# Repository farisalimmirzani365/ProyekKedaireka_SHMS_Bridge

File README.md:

# PCB-Desain Structur Health Monitoring System
Proyek Kedaireka "Solusi IoT untuk Memantau Kondisi Infrastruktur Jembatan". Kedaireka adalah proyek penelitian matching fund oleh Kementerian Pendidikan, Kebudayaan, Riset, dan Teknologi antara PT. INTI & Telkom University.

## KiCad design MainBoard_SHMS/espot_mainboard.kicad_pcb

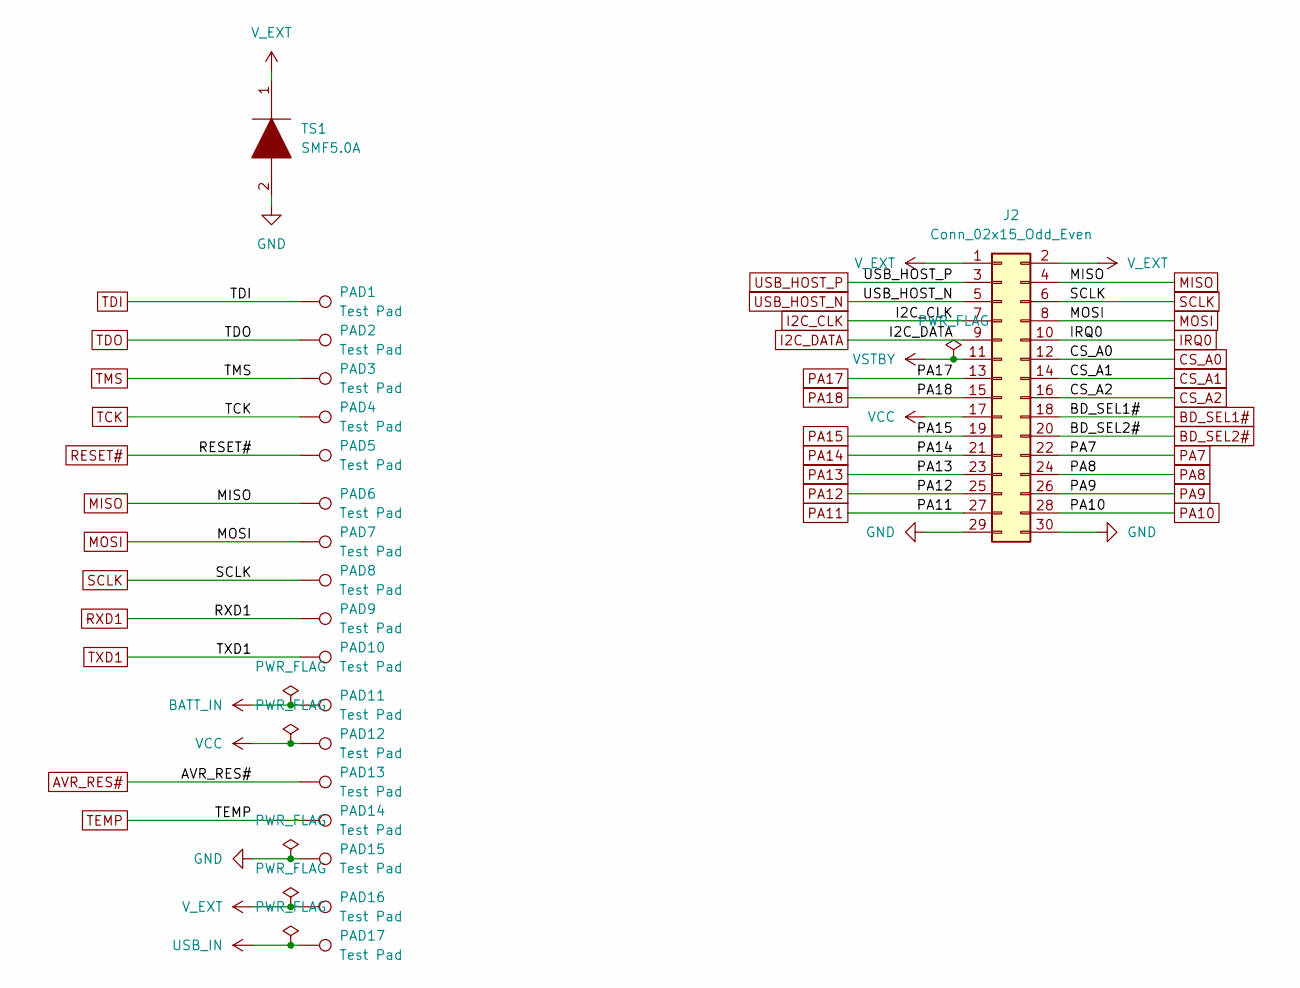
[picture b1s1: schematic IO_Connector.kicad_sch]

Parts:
J2: Conn_02x15_Odd_Even; PinHeader_2x15_P2.54mm_Vertical
PAD1, PAD2, PAD3, PAD4, PAD5, PAD6, PAD7, PAD8, PAD9, PAD10, PAD11, PAD12, PAD13, PAD14, PAD15, PAD16, PAD17: Test Pad; TestPoint_Pad_D4.0mm
TS1: SMF5.0A; SODFL3618X110N; Manufacturer_Part_Number SMF5.0A; Mouser Part Number 576-SMF5.0A

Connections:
AVR_RES#: PAD13.1; also elsewhere on the board
BATT_IN: PAD11.1; also elsewhere on the board
BD_SEL1#: J2.18; also elsewhere on the board
BD_SEL2#: J2.20; also elsewhere on the board
CS_A0: J2.12; also elsewhere on the board
CS_A1: J2.14; also elsewhere on the board
CS_A2: J2.16; also elsewhere on the board
GND: J2.29, J2.30, PAD15.1, TS1.2; also elsewhere on the board
I2C_CLK: J2.7; also elsewhere on the board
I2C_DATA: J2.9; also elsewhere on the board
IRQ0: J2.10; also elsewhere on the board
MISO: J2.4, PAD6.1; also elsewhere on the board
MOSI: J2.8, PAD7.1; also elsewhere on the board
PA7: J2.22; also elsewhere on the board
PA8: J2.24; also elsewhere on the board
PA9: J2.26; also elsewhere on the board
PA10: J2.28; also elsewhere on the board
PA11: J2.27; also elsewhere on the board
PA12: J2.25; also elsewhere on the board
PA13: J2.23; also elsewhere on the board
PA14: J2.21; also elsewhere on the board
PA15: J2.19; also elsewhere on the board
PA17: J2.13; also elsewhere on the board
PA18: J2.15; also elsewhere on the board
RESET#: PAD5.1; also elsewhere on the board
RXD1: PAD9.1; also elsewhere on the board
SCLK: J2.6, PAD8.1; also elsewhere on the board
TCK: PAD4.1; also elsewhere on the board
TDI: PAD1.1; also elsewhere on the board
TDO: PAD2.1; also elsewhere on the board
TEMP: PAD14.1; also elsewhere on the board
TMS: PAD3.1; also elsewhere on the board
TXD1: PAD10.1; also elsewhere on the board
USB_HOST_N: J2.5; also elsewhere on the board
USB_HOST_P: J2.3; also elsewhere on the board
USB_IN: PAD17.1; also elsewhere on the board
VCC: J2.17, PAD12.1; also elsewhere on the board
VSTBY: J2.11; also elsewhere on the board
V_EXT: J2.1, J2.2, PAD16.1, TS1.1; also elsewhere on the board

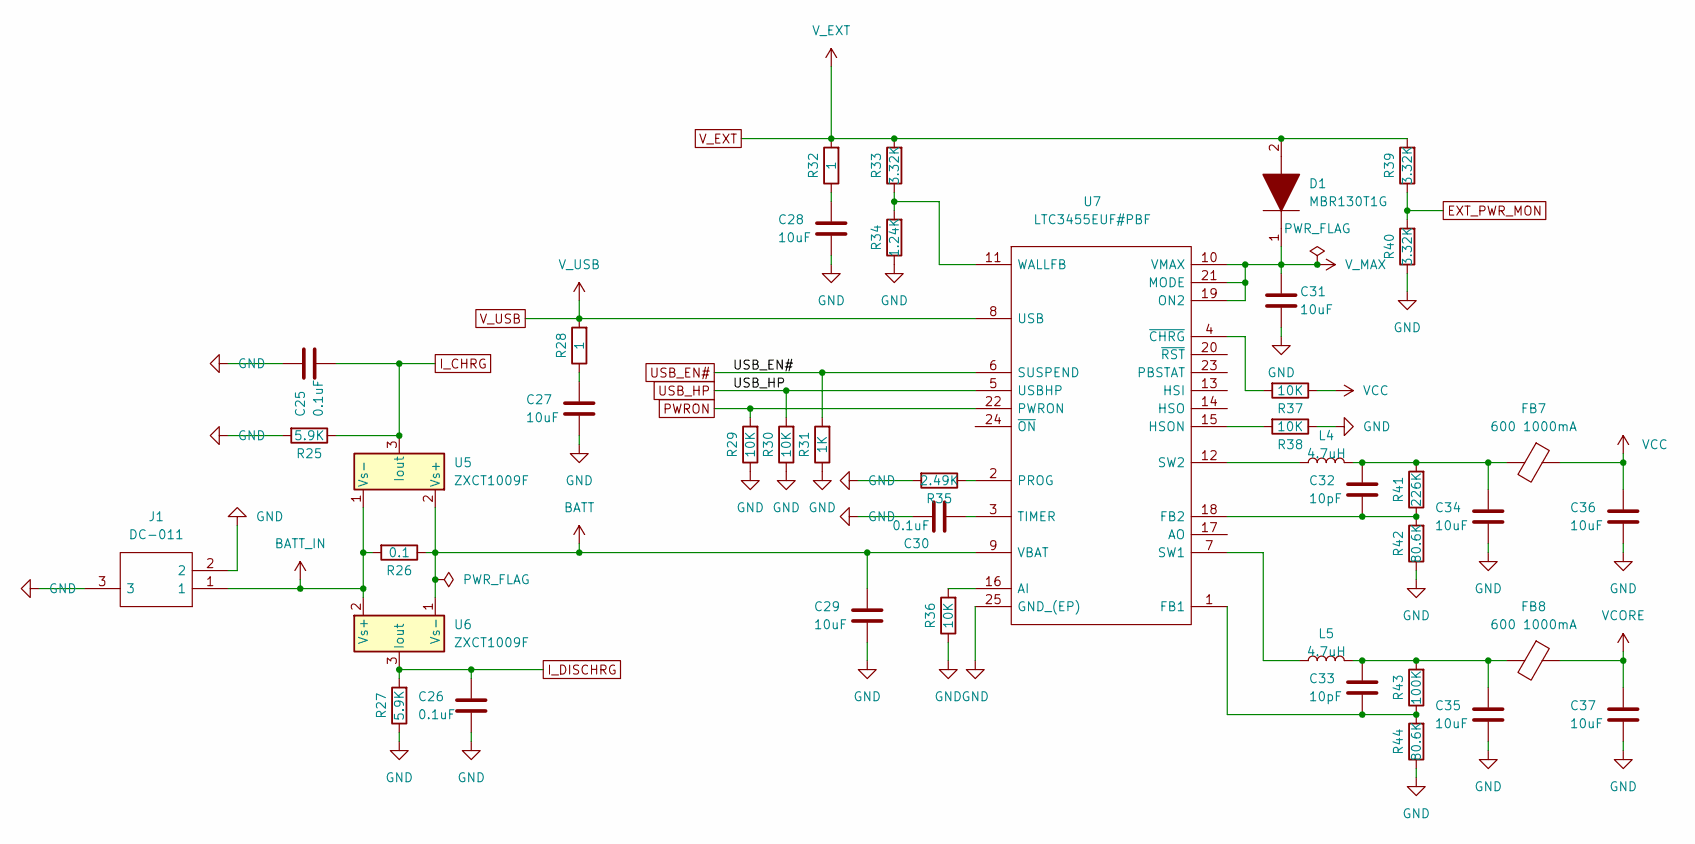
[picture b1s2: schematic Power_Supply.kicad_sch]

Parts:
C25, C26, C30: 0.1uF; C_0603_1608Metric_Pad1.08x0.95mm_HandSolder
C27, C28, C29, C31, C34, C35, C36, C37: 10uF; C_0603_1608Metric_Pad1.08x0.95mm_HandSolder
C32, C33: 10pF; C_0603_1608Metric_Pad1.08x0.95mm_HandSolder
D1: MBR130T1G; SOD3716X135N; Manufacturer_Part_Number MBR130T1G; Mouser Part Number 863-MBR130T1G
FB7, FB8: 600 1000mA; L_0603_1608Metric_Pad1.05x0.95mm_HandSolder
J1: DC-011; DC011; Manufacturer_Part_Number DC-011
L4, L5: 4.7uH; L_12x12mm_H6mm
R25, R27: 5.9K; R_0603_1608Metric_Pad0.98x0.95mm_HandSolder
R26: 0.1; R_0603_1608Metric_Pad0.98x0.95mm_HandSolder
R28, R32: 1; R_0603_1608Metric_Pad0.98x0.95mm_HandSolder
R29, R30, R36, R37, R38: 10K; R_0603_1608Metric_Pad0.98x0.95mm_HandSolder
R31: 1K; R_0603_1608Metric_Pad0.98x0.95mm_HandSolder
R33, R39, R40: 3.32K; R_0603_1608Metric_Pad0.98x0.95mm_HandSolder
R34: 1.24K; R_0603_1608Metric_Pad0.98x0.95mm_HandSolder
R35: 2.49K; R_0603_1608Metric_Pad0.98x0.95mm_HandSolder
R41: 226K; R_0603_1608Metric_Pad0.98x0.95mm_HandSolder
R42, R44: 80.6K; R_0603_1608Metric_Pad0.98x0.95mm_HandSolder
R43: 100K; R_0603_1608Metric_Pad0.98x0.95mm_HandSolder
U5, U6: ZXCT1009F; SOT-23
U7: LTC3455EUF#PBF; QFN50P400X400X80-25N-D; Manufacturer_Part_Number LTC3455EUF#PBF; Mouser Part Number 584-LTC3455EUF#PBF

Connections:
BATT: C29.1, R26.1, U5.2 (Vs+), U6.1 (Vs-), U7.9 (VBAT); also elsewhere on the board
BATT_IN: J1.1, R26.2, U5.1 (Vs-), U6.2 (Vs+); also elsewhere on the board
EXT_PWR_MON: R39.1, R40.2; also elsewhere on the board
GND: C25.1, C26.2, C27.2, C28.2, C29.2, C30.1, C31.2, C34.2, C35.2, C36.2, C37.2, J1.2, J1.3, R25.2, R27.1, R29.1, R30.1, R31.1, R34.1, R35.2, R36.1, R38.1, R40.1, R42.1, R44.1, U7.25 (GND_(EP)); also elsewhere on the board
I_CHRG: C25.2, R25.1, U5.3 (Iout); also elsewhere on the board
I_DISCHRG: C26.1, R27.2, U6.3 (Iout); also elsewhere on the board
unnamed: C27.1, R28.1
unnamed: C28.1, R32.1
unnamed: C30.2, U7.3 (TIMER)
unnamed: C32.1, C34.1, FB7.2, L4.2, R41.2
unnamed: C32.2, R41.1, R42.2, U7.18 (FB2)
unnamed: C33.1, C35.1, FB8.2, L5.2, R43.2
unnamed: C33.2, R43.1, R44.2, U7.1 (FB1)
unnamed: L4.1, U7.12 (SW2)
unnamed: L5.1, U7.7 (SW1)
unnamed: R33.1, R34.2, U7.11 (WALLFB)
unnamed: R35.1, U7.2 (PROG)
unnamed: R36.2, U7.16 (AI)
unnamed: R37.2, U7.4 (~CHRG)
unnamed: R38.2, U7.15 (HSON)
PWRON: R29.2, U7.22 (PWRON); also elsewhere on the board
USB_EN#: R31.2, U7.6 (SUSPEND); also elsewhere on the board
USB_HP: R30.2, U7.5 (USBHP); also elsewhere on the board
USB_IN: R28.2, U7.8 (USB); also elsewhere on the board
VCC: C36.1, FB7.1, R37.1; also elsewhere on the board
VCORE: C37.1, FB8.1; also elsewhere on the board
V_EXT: D1.2, R32.2, R33.2, R39.2; also elsewhere on the board
V_MAX: C31.1, D1.1, U7.10 (VMAX), U7.19 (ON2), U7.21 (MODE); also elsewhere on the board

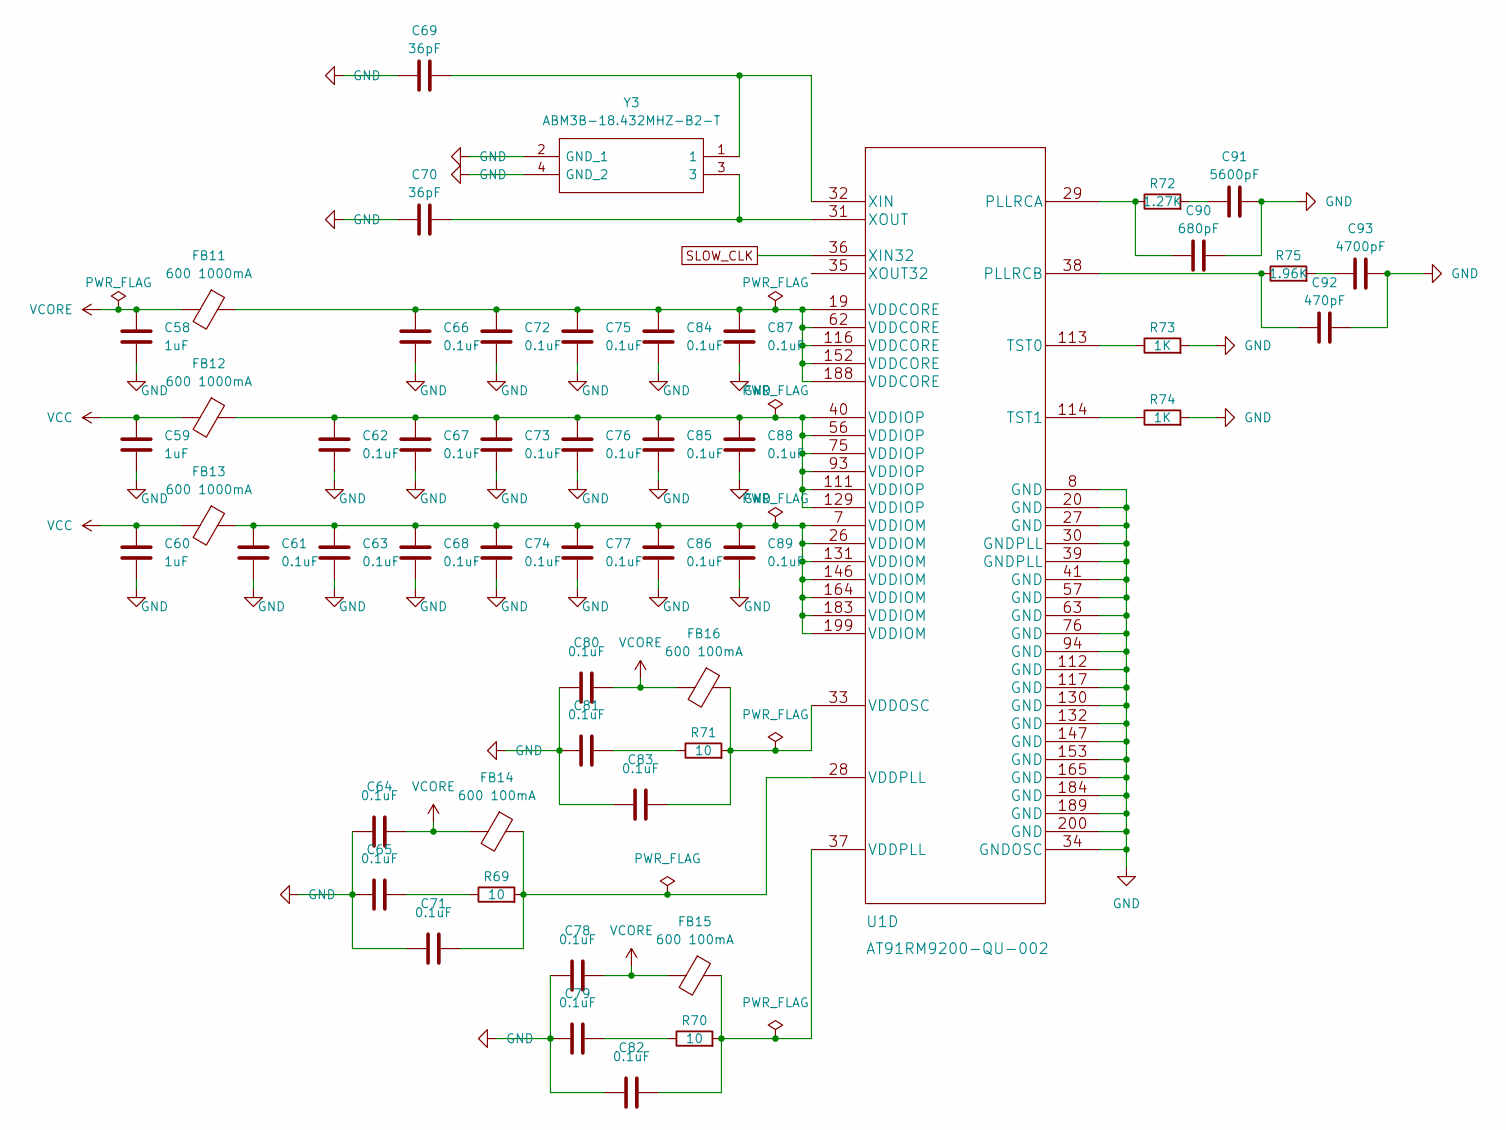
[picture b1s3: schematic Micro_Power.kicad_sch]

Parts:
C58, C59, C60: 1uF; C_0603_1608Metric_Pad1.08x0.95mm_HandSolder
C61, C62, C63, C64, C65, C66, C67, C68, C71, C72, C73, C74, C75, C76, C77, C78, C79, C80, C81, C82, C83, C84, C85, C86, C87, C88, C89: 0.1uF; C_0603_1608Metric_Pad1.08x0.95mm_HandSolder
C69, C70: 36pF; C_0603_1608Metric_Pad1.08x0.95mm_HandSolder
C90: 680pF; C_0603_1608Metric_Pad1.08x0.95mm_HandSolder
C91: 5600pF; C_0603_1608Metric_Pad1.08x0.95mm_HandSolder
C92: 470pF; C_0603_1608Metric_Pad1.08x0.95mm_HandSolder
C93: 4700pF; C_0603_1608Metric_Pad1.08x0.95mm_HandSolder
FB11, FB12, FB13: 600 1000mA; L_0603_1608Metric_Pad1.05x0.95mm_HandSolder
FB14, FB15, FB16: 600 100mA; L_0402_1005Metric_Pad0.77x0.64mm_HandSolder
R69, R70, R71: 10; R_0603_1608Metric_Pad0.98x0.95mm_HandSolder
R72: 1.27K; R_0603_1608Metric_Pad0.98x0.95mm_HandSolder
R73, R74: 1K; R_0603_1608Metric_Pad0.98x0.95mm_HandSolder
R75: 1.96K; R_0603_1608Metric_Pad0.98x0.95mm_HandSolder
U1: AT91RM9200-QU-002; PQFP208_ATM
Y3: ABM3B-18.432MHZ-B2-T; ABM3B8000MHZ101UT; Manufacturer_Part_Number ABM3B-18.432MHZ-B2-T; Mouser Part Number 815-ABM3B-18.432-B2

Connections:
GND: C58.2, C59.2, C60.2, C61.2, C62.2, C63.2, C64.1, C65.1, C66.2, C67.2, C68.2, C69.2, C70.2, C71.1, C72.2, C73.2, C74.2, C75.2, C76.2, C77.2, C78.1, C79.1, C80.1, C81.1, C82.1, C83.1, C84.2, C85.2, C86.2, C87.2, C88.2, C89.2, C90.1, C91.1, C92.1, C93.1, R73.2, R74.2, U1.8 (GND), U1.20 (GND), U1.27 (GND), U1.30 (GNDPLL), U1.34 (GNDOSC), U1.39 (GNDPLL), U1.41 (GND), U1.57 (GND), U1.63 (GND), U1.76 (GND), U1.94 (GND), U1.112 (GND), U1.117 (GND), U1.130 (GND), U1.132 (GND), U1.147 (GND), U1.153 (GND), U1.165 (GND), U1.184 (GND), U1.189 (GND), U1.200 (GND), Y3.2 (GND_1), Y3.4 (GND_2); also elsewhere on the board
unnamed: C61.1, C63.1, C68.1, C74.1, C77.1, C86.1, C89.1, FB13.1, U1.7 (VDDIOM), U1.26 (VDDIOM), U1.131 (VDDIOM), U1.146 (VDDIOM), U1.164 (VDDIOM), U1.183 (VDDIOM), U1.199 (VDDIOM)
unnamed: C62.1, C67.1, C73.1, C76.1, C85.1, C88.1, FB12.1, U1.40 (VDDIOP), U1.56 (VDDIOP), U1.75 (VDDIOP), U1.93 (VDDIOP), U1.111 (VDDIOP), U1.129 (VDDIOP)
unnamed: C65.2, R69.1
unnamed: C66.1, C72.1, C75.1, C84.1, C87.1, FB11.1, U1.19 (VDDCORE), U1.62 (VDDCORE), U1.116 (VDDCORE), U1.152 (VDDCORE), U1.188 (VDDCORE)
unnamed: C69.1, U1.32 (XIN), Y3.1
unnamed: C70.1, U1.31 (XOUT), Y3.3
unnamed: C71.2, FB14.1, R69.2, U1.28 (VDDPLL)
unnamed: C79.2, R70.1
unnamed: C81.2, R71.1
unnamed: C82.2, FB15.1, R70.2, U1.37 (VDDPLL)
unnamed: C83.2, FB16.1, R71.2, U1.33 (VDDOSC)
unnamed: C90.2, R72.1, U1.29 (PLLRCA)
unnamed: C91.2, R72.2
unnamed: C92.2, R75.1, U1.38 (PLLRCB)
unnamed: C93.2, R75.2
unnamed: R73.1, U1.113 (TST0)
unnamed: R74.1, U1.114 (TST1)
SLOW_CLK: U1.36 (XIN32); also elsewhere on the board
VCC: C59.1, C60.1, FB12.2, FB13.2; also elsewhere on the board
VCORE: C58.1, C64.2, C78.2, C80.2, FB11.2, FB14.2, FB15.2, FB16.2; also elsewhere on the board

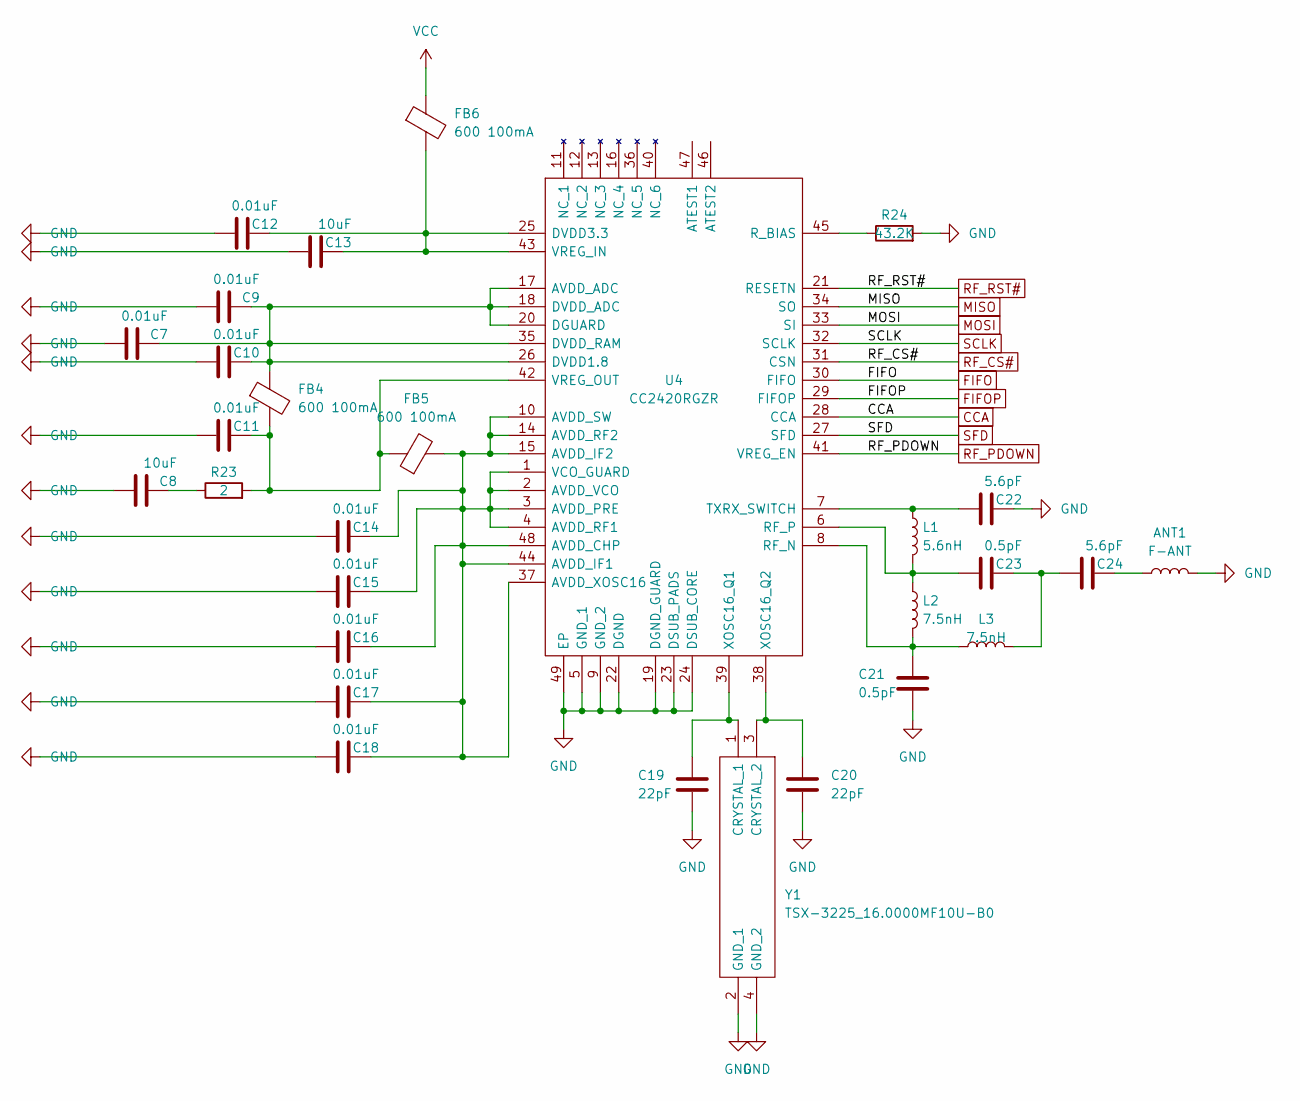
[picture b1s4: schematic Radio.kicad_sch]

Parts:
ANT1: F-ANT; L_0805_2012Metric_Pad1.05x1.20mm_HandSolder
C7, C9, C10, C11, C12, C14, C15, C16, C17, C18: 0.01uF; C_0603_1608Metric_Pad1.08x0.95mm_HandSolder
C8, C13: 10uF; C_0603_1608Metric_Pad1.08x0.95mm_HandSolder
C19, C20: 22pF; C_0603_1608Metric_Pad1.08x0.95mm_HandSolder
C21, C23: 0.5pF; C_0603_1608Metric_Pad1.08x0.95mm_HandSolder
C22, C24: 5.6pF; C_0603_1608Metric_Pad1.08x0.95mm_HandSolder
FB4, FB5, FB6: 600 100mA; L_0402_1005Metric_Pad0.77x0.64mm_HandSolder
L1: 5.6nH; L_0603_1608Metric_Pad1.05x0.95mm_HandSolder
L2, L3: 7.5nH; L_0603_1608Metric_Pad1.05x0.95mm_HandSolder
R23: 2; R_0603_1608Metric_Pad0.98x0.95mm_HandSolder
R24: 43.2K; R_0603_1608Metric_Pad0.98x0.95mm_HandSolder
U4: CC2420RGZR; QFN50P700X700X100-49N-D; Manufacturer_Part_Number CC2420RGZR; Mouser Part Number 595-CC2420RGZR
Y1: TSX-3225_16.0000MF10U-B0; TSX3225240000MF20GAC0; Manufacturer_Part_Number TSX-3225 16.0000MF10U-B0; Mouser Part Number 732-322516MF10U-B0

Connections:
CCA: U4.28 (CCA); also elsewhere on the board
FIFO: U4.30 (FIFO); also elsewhere on the board
FIFOP: U4.29 (FIFOP); also elsewhere on the board
GND: ANT1.2, C7.1, C8.1, C9.1, C10.1, C11.1, C12.1, C13.1, C14.1, C15.1, C16.1, C17.1, C18.1, C19.2, C20.2, C21.2, C22.2, R24.2, U4.5 (GND_1), U4.9 (GND_2), U4.19 (DGND_GUARD), U4.22 (DGND), U4.23 (DSUB_PADS), U4.24 (DSUB_CORE), U4.49 (EP), Y1.2 (GND_1), Y1.4 (GND_2); also elsewhere on the board
MISO: U4.34 (SO); also elsewhere on the board
MOSI: U4.33 (SI); also elsewhere on the board
unnamed: ANT1.1, C24.2
unnamed: C8.2, R23.1
unnamed: C7.2, C9.2, C10.2, FB4.1, U4.17 (AVDD_ADC), U4.18 (DVDD_ADC), U4.20 (DGUARD), U4.26 (DVDD1.8), U4.35 (DVDD_RAM)
unnamed: C11.2, FB4.2, FB5.1, R23.2, U4.42 (VREG_OUT)
unnamed: C12.2, C13.2, FB6.2, U4.25 (DVDD3.3), U4.43 (VREG_IN)
unnamed: C14.2, C15.2, C16.2, C17.2, C18.2, FB5.2, U4.1 (VCO_GUARD), U4.2 (AVDD_VCO), U4.3 (AVDD_PRE), U4.4 (AVDD_RF1), U4.10 (AVDD_SW), U4.14 (AVDD_RF2), U4.15 (AVDD_IF2), U4.37 (AVDD_XOSC16), U4.44 (AVDD_IF1), U4.48 (AVDD_CHP)
unnamed: C19.1, U4.39 (XOSC16_Q1), Y1.1 (CRYSTAL_1)
unnamed: C20.1, U4.38 (XOSC16_Q2), Y1.3 (CRYSTAL_2)
unnamed: C21.1, L2.2, L3.1, U4.8 (RF_N)
unnamed: C22.1, L1.1, U4.7 (TXRX_SWITCH)
unnamed: C23.1, L1.2, L2.1, U4.6 (RF_P)
unnamed: C23.2, C24.1, L3.2
unnamed: R24.1, U4.45 (R_BIAS)
RF_CS#: U4.31 (CSN); also elsewhere on the board
RF_PDOWN: U4.41 (VREG_EN); also elsewhere on the board
RF_RST#: U4.21 (RESETN); also elsewhere on the board
SCLK: U4.32 (SCLK); also elsewhere on the board
SFD: U4.27 (SFD); also elsewhere on the board
VCC: FB6.1; also elsewhere on the board

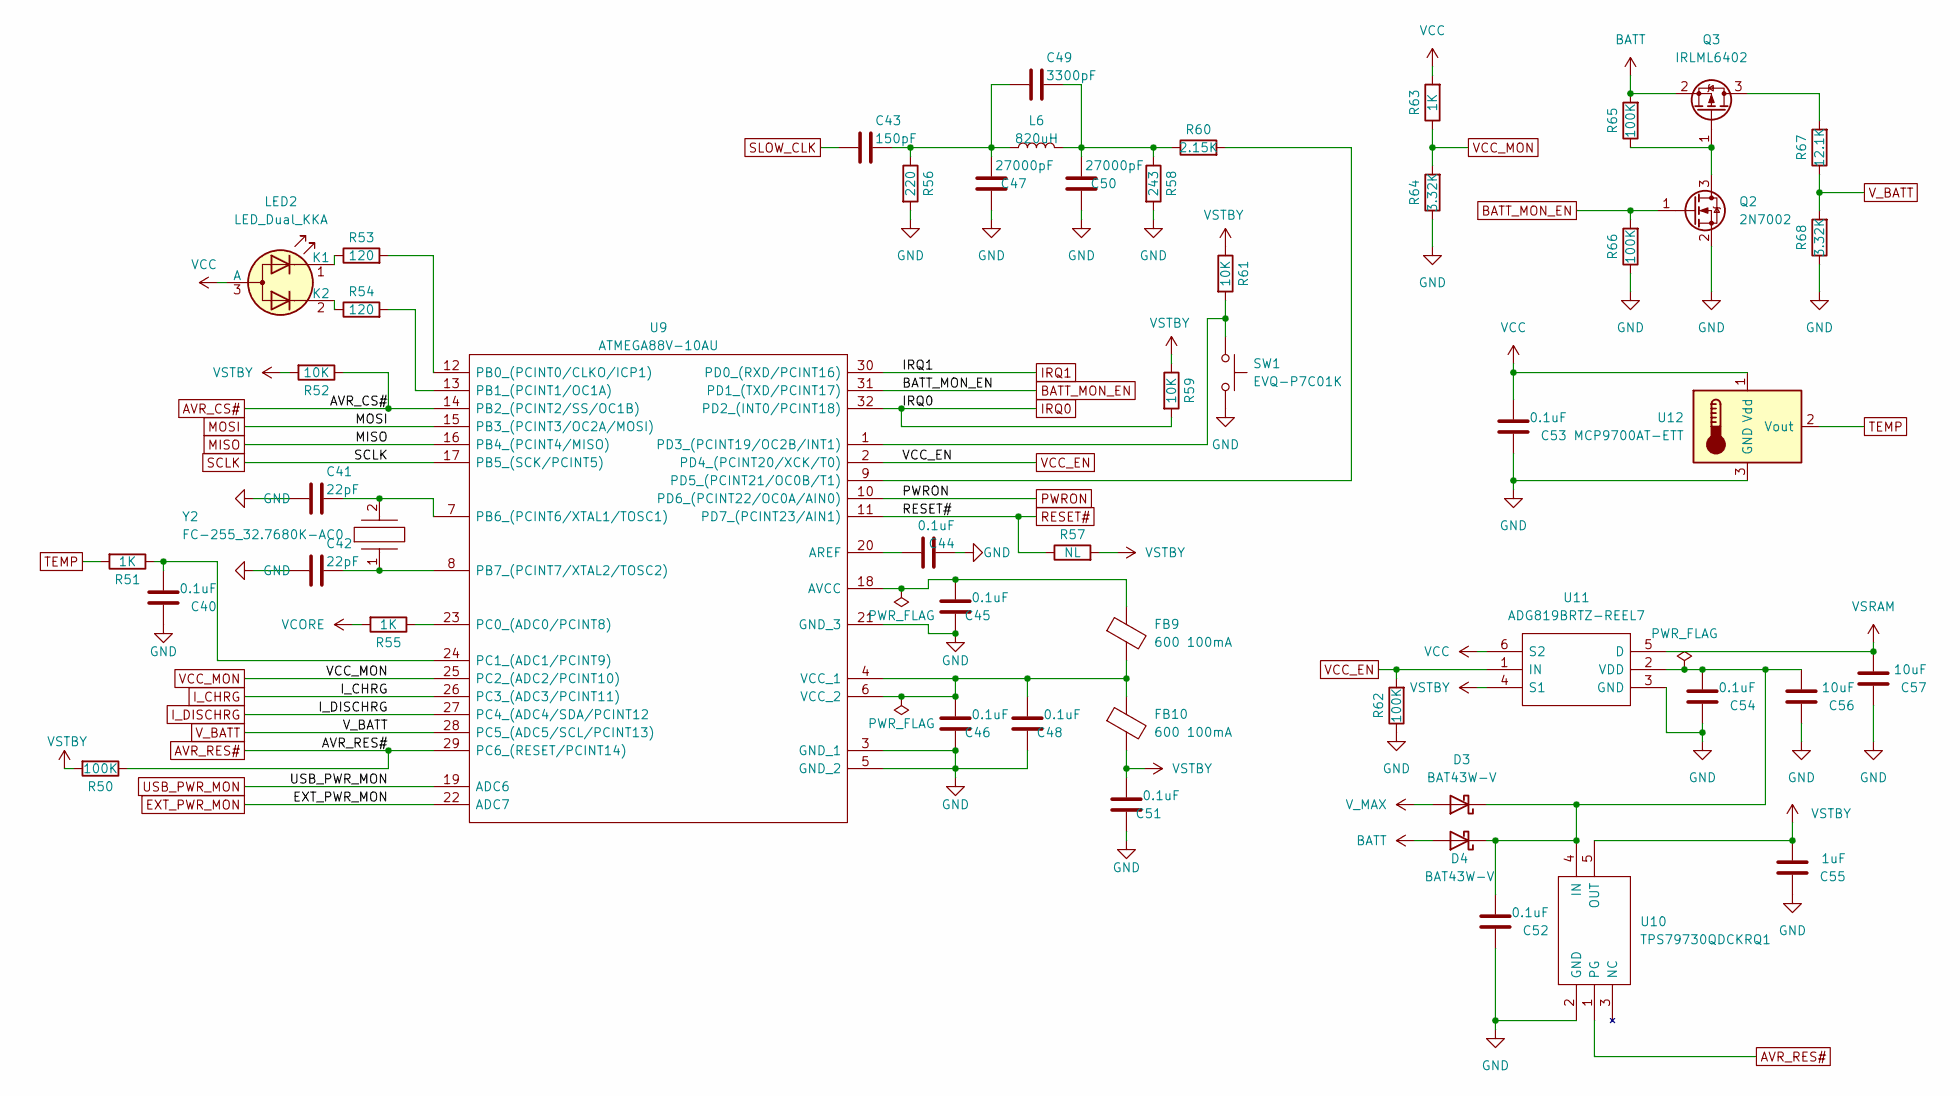
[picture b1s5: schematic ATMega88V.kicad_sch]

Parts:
C40, C44, C45, C46, C48, C51, C52, C53, C54: 0.1uF; C_0603_1608Metric_Pad1.08x0.95mm_HandSolder
C41, C42: 22pF; C_0603_1608Metric_Pad1.08x0.95mm_HandSolder
C43: 150pF; C_0603_1608Metric_Pad1.08x0.95mm_HandSolder
C47, C50: 27000pF; C_0603_1608Metric_Pad1.08x0.95mm_HandSolder
C49: 3300pF; C_0603_1608Metric_Pad1.08x0.95mm_HandSolder
C55: 1uF; C_0603_1608Metric_Pad1.08x0.95mm_HandSolder
C56, C57: 10uF; C_0603_1608Metric_Pad1.08x0.95mm_HandSolder
D3, D4: BAT43W-V; D_SOD-123
FB9, FB10: 600 100mA; L_0402_1005Metric_Pad0.77x0.64mm_HandSolder
L6: 820uH; L_10.4x10.4_H4.8
LED2: LED_Dual_KKA; LED_LiteOn_LTST-S326
Q2: 2N7002; SOT-23
Q3: IRLML6402; SOT-23
R50, R62, R65, R66: 100K; R_0603_1608Metric_Pad0.98x0.95mm_HandSolder
R51, R55, R63: 1K; R_0603_1608Metric_Pad0.98x0.95mm_HandSolder
R52, R59, R61: 10K; R_0603_1608Metric_Pad0.98x0.95mm_HandSolder
R53, R54: 120; R_0603_1608Metric_Pad0.98x0.95mm_HandSolder
R56: 220; R_0603_1608Metric_Pad0.98x0.95mm_HandSolder
R57: NL; R_0603_1608Metric_Pad0.98x0.95mm_HandSolder
R58: 243; R_0603_1608Metric_Pad0.98x0.95mm_HandSolder
R60: 2.15K; R_0603_1608Metric_Pad0.98x0.95mm_HandSolder
R64, R68: 3.32K; R_0603_1608Metric_Pad0.98x0.95mm_HandSolder
R67: 12.1K; R_0603_1608Metric_Pad0.98x0.95mm_HandSolder
SW1: EVQ-P7C01K; SW_SPST_EVQP7C
U9: ATMEGA88V-10AU; QFP80P900X900X120-32N; Manufacturer_Part_Number ATMEGA88V-10AU; Mouser Part Number 556-ATMEGA88V10AU
U10: TPS79730QDCKRQ1; SOT65P210X110-5N; Manufacturer_Part_Number TPS79730QDCKRQ1; Mouser Part Number 595-TPS79730QDCKRQ1
U11: ADG819BRTZ-REEL7; SOT95P280X145-6N; Manufacturer_Part_Number ADG819BRTZ-REEL7; Mouser Part Number 584-ADG819BRTZ-R7
U12: MCP9700AT-ETT; SOT-23
Y2: FC-255_32.7680K-AC0; FC-255; Manufacturer_Part_Number FC-255 32.7680K-AC0

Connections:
AVR_CS#: R52.1, U9.14 (PB2_(PCINT2/SS/OC1B))
AVR_RES#: R50.1, U9.29 (PC6_(RESET/PCINT14)), U10.1 (PG); also elsewhere on the board
BATT: D4.2 (A), Q3.2 (S), R65.2; also elsewhere on the board
BATT_MON_EN: Q2.1 (G), R66.2, U9.31 (PD1_(TXD/PCINT17))
EXT_PWR_MON: U9.22 (ADC7); also elsewhere on the board
GND: C40.1, C41.2, C42.2, C44.2, C45.1, C46.1, C47.1, C48.1, C50.1, C51.1, C52.1, C53.1, C54.1, C55.1, C56.1, C57.1, Q2.2 (S), R56.2, R58.2, R62.1, R64.1, R66.1, R68.1, SW1.2, U9.3 (GND_1), U9.5 (GND_2), U9.21 (GND_3), U10.2 (GND), U11.3 (GND), U12.3 (GND); also elsewhere on the board
IRQ0: R59.2, U9.32 (PD2_(INT0/PCINT18)); also elsewhere on the board
IRQ1: U9.30 (PD0_(RXD/PCINT16)); also elsewhere on the board
I_CHRG: U9.26 (PC3_(ADC3/PCINT11)); also elsewhere on the board
I_DISCHRG: U9.27 (PC4_(ADC4/SDA/PCINT12); also elsewhere on the board
MISO: U9.16 (PB4_(PCINT4/MISO)); also elsewhere on the board
MOSI: U9.15 (PB3_(PCINT3/OC2A/MOSI)); also elsewhere on the board
unnamed: C40.2, R51.1, U9.24 (PC1_(ADC1/PCINT9))
unnamed: C41.1, U9.7 (PB6_(PCINT6/XTAL1/TOSC1)), Y2.2
unnamed: C42.1, U9.8 (PB7_(PCINT7/XTAL2/TOSC2)), Y2.1
unnamed: C43.1, C47.2, C49.2, L6.1, R56.1
unnamed: C44.1, U9.20 (AREF)
unnamed: C45.2, FB9.1, U9.18 (AVCC)
unnamed: C46.2, C48.2, FB9.2, FB10.1, U9.4 (VCC_1), U9.6 (VCC_2)
unnamed: C49.1, C50.2, L6.2, R58.1, R60.1
unnamed: C52.2, C54.2, C56.2, D3.1 (K), D4.1 (K), U10.4 (IN), U11.2 (VDD)
unnamed: LED2.1 (K1), R53.1
unnamed: LED2.2 (K2), R54.1
unnamed: Q2.3 (D), Q3.1 (G), R65.1
unnamed: Q3.3 (D), R67.2
unnamed: R53.2, U9.12 (PB0_(PCINT0/CLKO/ICP1))
unnamed: R54.2, U9.13 (PB1_(PCINT1/OC1A))
unnamed: R55.1, U9.23 (PC0_(ADC0/PCINT8))
unnamed: R60.2, U9.9 (PD5_(PCINT21/OC0B/T1))
unnamed: R61.2, SW1.1, U9.1 (PD3_(PCINT19/OC2B/INT1))
PWRON: U9.10 (PD6_(PCINT22/OC0A/AIN0)); also elsewhere on the board
RESET#: R57.1, U9.11 (PD7_(PCINT23/AIN1)); also elsewhere on the board
SCLK: U9.17 (PB5_(SCK/PCINT5)); also elsewhere on the board
SLOW_CLK: C43.2; also elsewhere on the board
TEMP: R51.2, U12.2 (Vout); also elsewhere on the board
USB_PWR_MON: U9.19 (ADC6); also elsewhere on the board
VCC: C53.2, LED2.3 (A), R63.2, U11.6 (S2), U12.1 (Vdd); also elsewhere on the board
VCC_EN: R62.2, U9.2 (PD4_(PCINT20/XCK/T0)), U11.1 (IN)
VCC_MON: R63.1, R64.2, U9.25 (PC2_(ADC2/PCINT10))
VCORE: R55.2; also elsewhere on the board
VSRAM: C57.2, U11.5 (D); also elsewhere on the board
VSTBY: C51.2, C55.2, FB10.2, R50.2, R52.2, R57.2, R59.1, R61.1, U10.5 (OUT), U11.4 (S1); also elsewhere on the board
V_BATT: R67.1, R68.2, U9.28 (PC5_(ADC5/SCL/PCINT13))
V_MAX: D3.2 (A); also elsewhere on the board

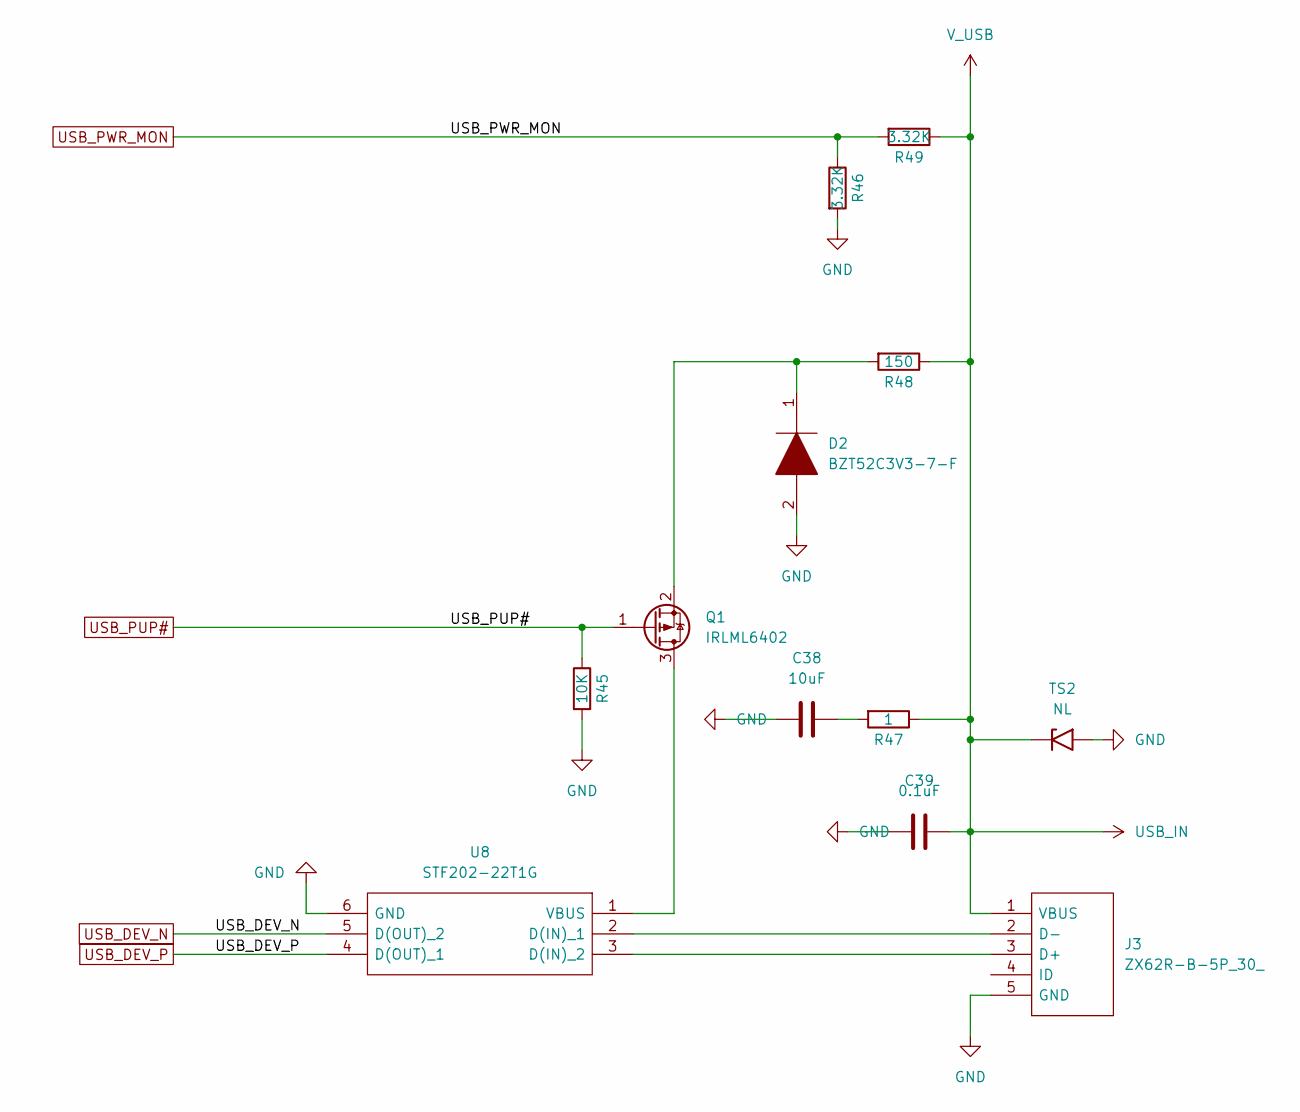
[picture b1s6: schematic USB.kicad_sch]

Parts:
C38: 10uF; C_0603_1608Metric_Pad1.08x0.95mm_HandSolder
C39: 0.1uF; C_0603_1608Metric_Pad1.08x0.95mm_HandSolder
D2: BZT52C3V3-7-F; SOD3716X145N; Manufacturer_Part_Number BZT52C3V3-7-F; Mouser Part Number 621-BZT52C3V3-F
J3: ZX62R-B-5P_30_; ZX62R-B-5P(30); Manufacturer_Part_Number ZX62R-B-5P(30); Mouser Part Number 798-ZX62R-B-5P30
Q1: IRLML6402; SOT-23
R45: 10K; R_0603_1608Metric_Pad0.98x0.95mm_HandSolder
R46, R49: 3.32K; R_0603_1608Metric_Pad0.98x0.95mm_HandSolder
R47: 1; R_0603_1608Metric_Pad0.98x0.95mm_HandSolder
R48: 150; R_0603_1608Metric_Pad0.98x0.95mm_HandSolder
TS2: NL; D_SMF
U8: STF202-22T1G; SOT95P275X110-6N; Manufacturer_Part_Number STF202-22T1G; Mouser Part Number 863-STF202-22T1G

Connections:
GND: C38.1, C39.1, D2.2, J3.5 (GND), R45.2, R46.2, TS2.2 (A2), U8.6 (GND); also elsewhere on the board
unnamed: C38.2, R47.2
unnamed: D2.1, Q1.2 (S), R48.2
unnamed: J3.2 (D-), U8.2 (D(IN)_1)
unnamed: J3.3 (D+), U8.3 (D(IN)_2)
unnamed: Q1.3 (D), U8.1 (VBUS)
USB_DEV_N: U8.5 (D(OUT)_2); also elsewhere on the board
USB_DEV_P: U8.4 (D(OUT)_1); also elsewhere on the board
USB_IN: C39.2, J3.1 (VBUS), R47.1, R48.1, R49.1, TS2.1 (A1); also elsewhere on the board
USB_PUP#: Q1.1 (G), R45.1; also elsewhere on the board
USB_PWR_MON: R46.1, R49.2; also elsewhere on the board

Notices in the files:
parts and their libraries:
Copyright 2021 Accelerated Designs. All rights reserved.
